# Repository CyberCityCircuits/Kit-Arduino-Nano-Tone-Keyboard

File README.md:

# Kit-Arduino-Nano-Tone-Keyboard

This is the repo for the Arduino Nano Tone Keyboard kit sold at https://shop.cybercitycircuits.com/products/arduino-nano-tone-keyboard-soldering-kit

This kit uses an Arduino Nano to make music with a circuit that is laid out like a musical keyboard.

|Pin|Description|

| --- | --- |

|00|Used for Serial Receive|

|01|Used for Serial Transmit|

|02|Speaker|

|03|NA|

|04|NA|

|05|NA|

|06|NA|

|07|NA|

|08|NA|

|09|NA|

|10|Button Column 1|

|11|Button Column 2|

|12|Button Column 3|

|13|LED|

|14|Button Column 4|

|15|Button Column 5|

|16|Button Column 6|

|17|Button Row 1|

|18|Button Row 2|

|19|Button Row 3|

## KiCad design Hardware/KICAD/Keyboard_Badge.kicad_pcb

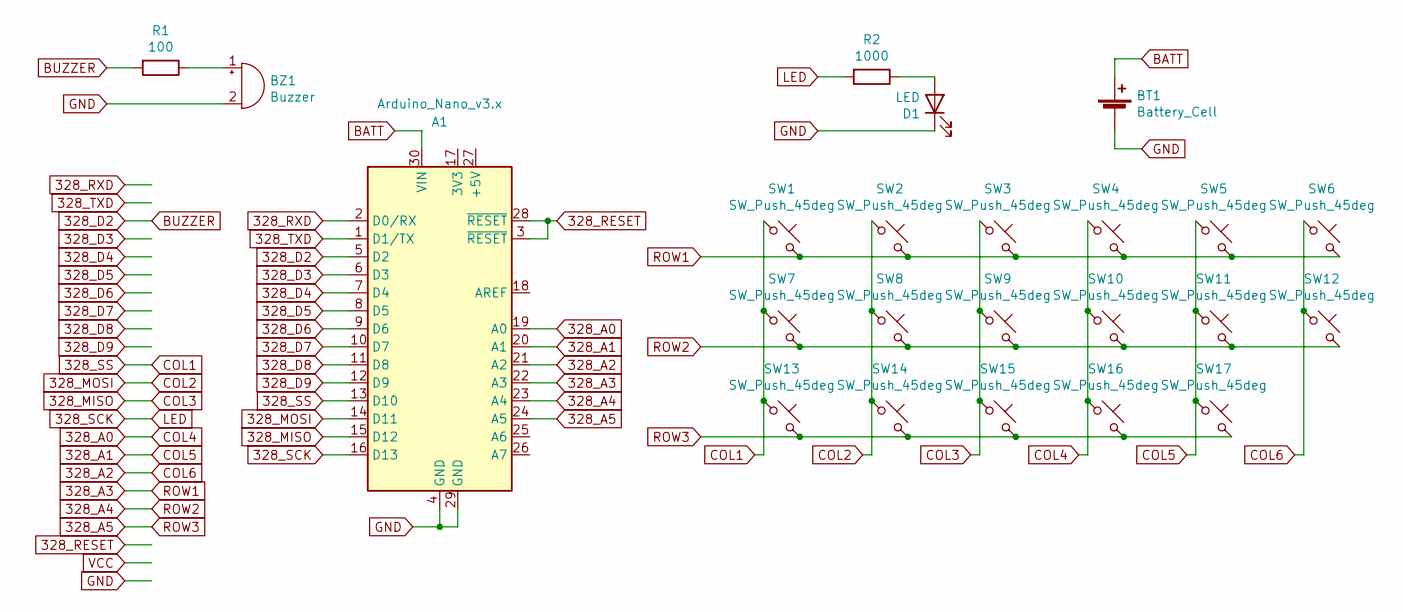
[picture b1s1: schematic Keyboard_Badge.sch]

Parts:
A1: Arduino_Nano_v3.x; Arduino_Nano
BT1: Battery_Cell; PinHeader_1x02_P2.54mm_Vertical
BZ1: Buzzer; Buzzer_12x9.5RM7.6
D1: LED; Schematic - LED 5mm(2.56P) 003
R1: 100; Schematic - Resistor 7.62mm
R2: 1000; Schematic - Resistor 7.62mm
SW1, SW2, SW3, SW4, SW5, SW6, SW7, SW8, SW9, SW10, SW11, SW12, SW13, SW14, SW15, SW16, SW17: SW_Push_45deg; Kailanda Push Button 6.5x4.5

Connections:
328_A0: A1.19 (A0), SW4.1, SW10.1, SW16.1
328_A1: A1.20 (A1), SW5.1, SW11.1, SW17.1
328_A2: A1.21 (A2), SW6.1, SW12.1
328_A3: A1.22 (A3), SW1.2, SW2.2, SW3.2, SW4.2, SW5.2, SW6.2
328_A4: A1.23 (A4), SW7.2, SW8.2, SW9.2, SW10.2, SW11.2, SW12.2
328_A5: A1.24 (A5), SW13.2, SW14.2, SW15.2, SW16.2, SW17.2
328_D2: A1.5 (D2), R1.2
328_D3: A1.6 (D3)
328_D4: A1.7 (D4)
328_D5: A1.8 (D5)
328_D6: A1.9 (D6)
328_D7: A1.10 (D7)
328_D8: A1.11 (D8)
328_D9: A1.12 (D9)
328_MISO: A1.15 (D12), SW3.1, SW9.1, SW15.1
328_MOSI: A1.14 (D11), SW2.1, SW8.1, SW14.1
328_RESET: A1.3 (~RESET), A1.28 (~RESET)
328_RXD: A1.2 (D0/RX)
328_SCK: A1.16 (D13), R2.2
328_SS: A1.13 (D10), SW1.1, SW7.1, SW13.1
328_TXD: A1.1 (D1/TX)
BATT: A1.30 (VIN), BT1.1 (+)
GND: A1.4 (GND), A1.29 (GND), BT1.2 (-), BZ1.2 (+), D1.1 (K)
unnamed: BZ1.1 (-), R1.1
unnamed: D1.2 (A), R2.1

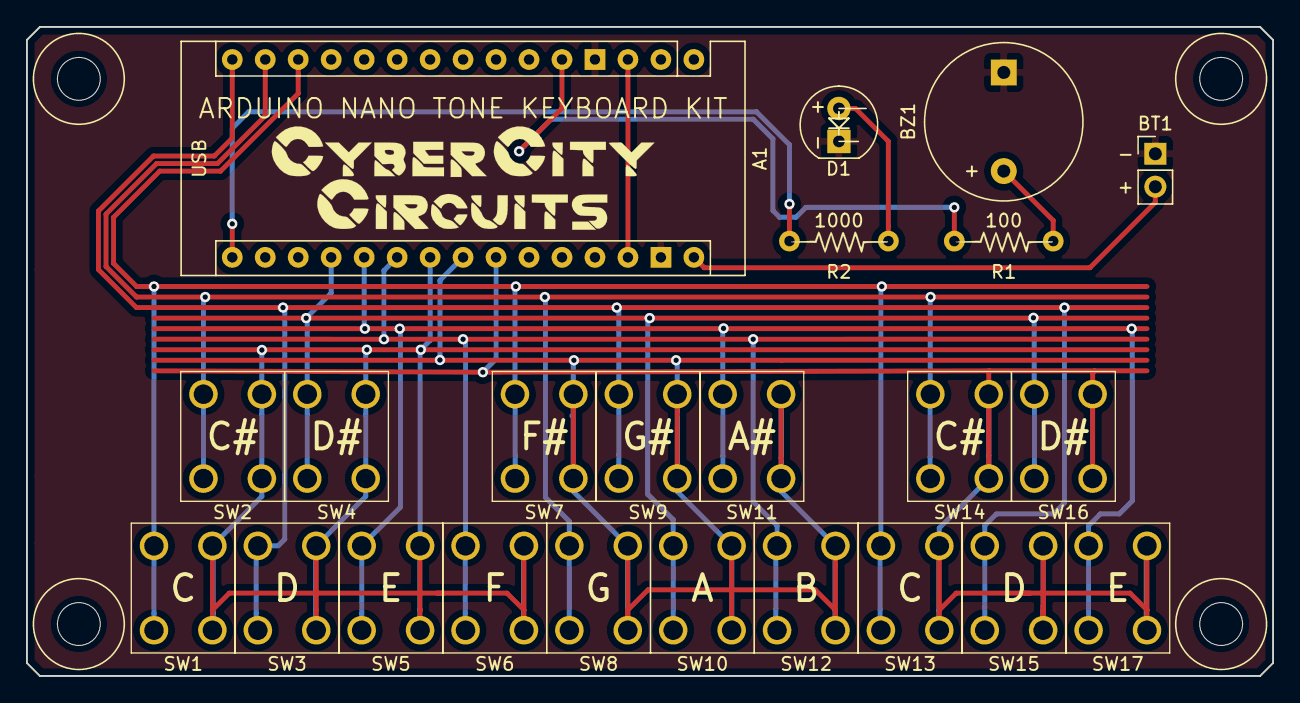
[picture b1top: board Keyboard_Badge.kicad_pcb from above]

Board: 2 copper layers, 96.0 x 50.0 mm, 27 parts (0 on the bottom side), 16 nets.

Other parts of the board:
 : 3mm_Hole; 3mm Mount Hole
 #2,  #3,  #4: 3mm_Hole; 3mm Mount Hole
